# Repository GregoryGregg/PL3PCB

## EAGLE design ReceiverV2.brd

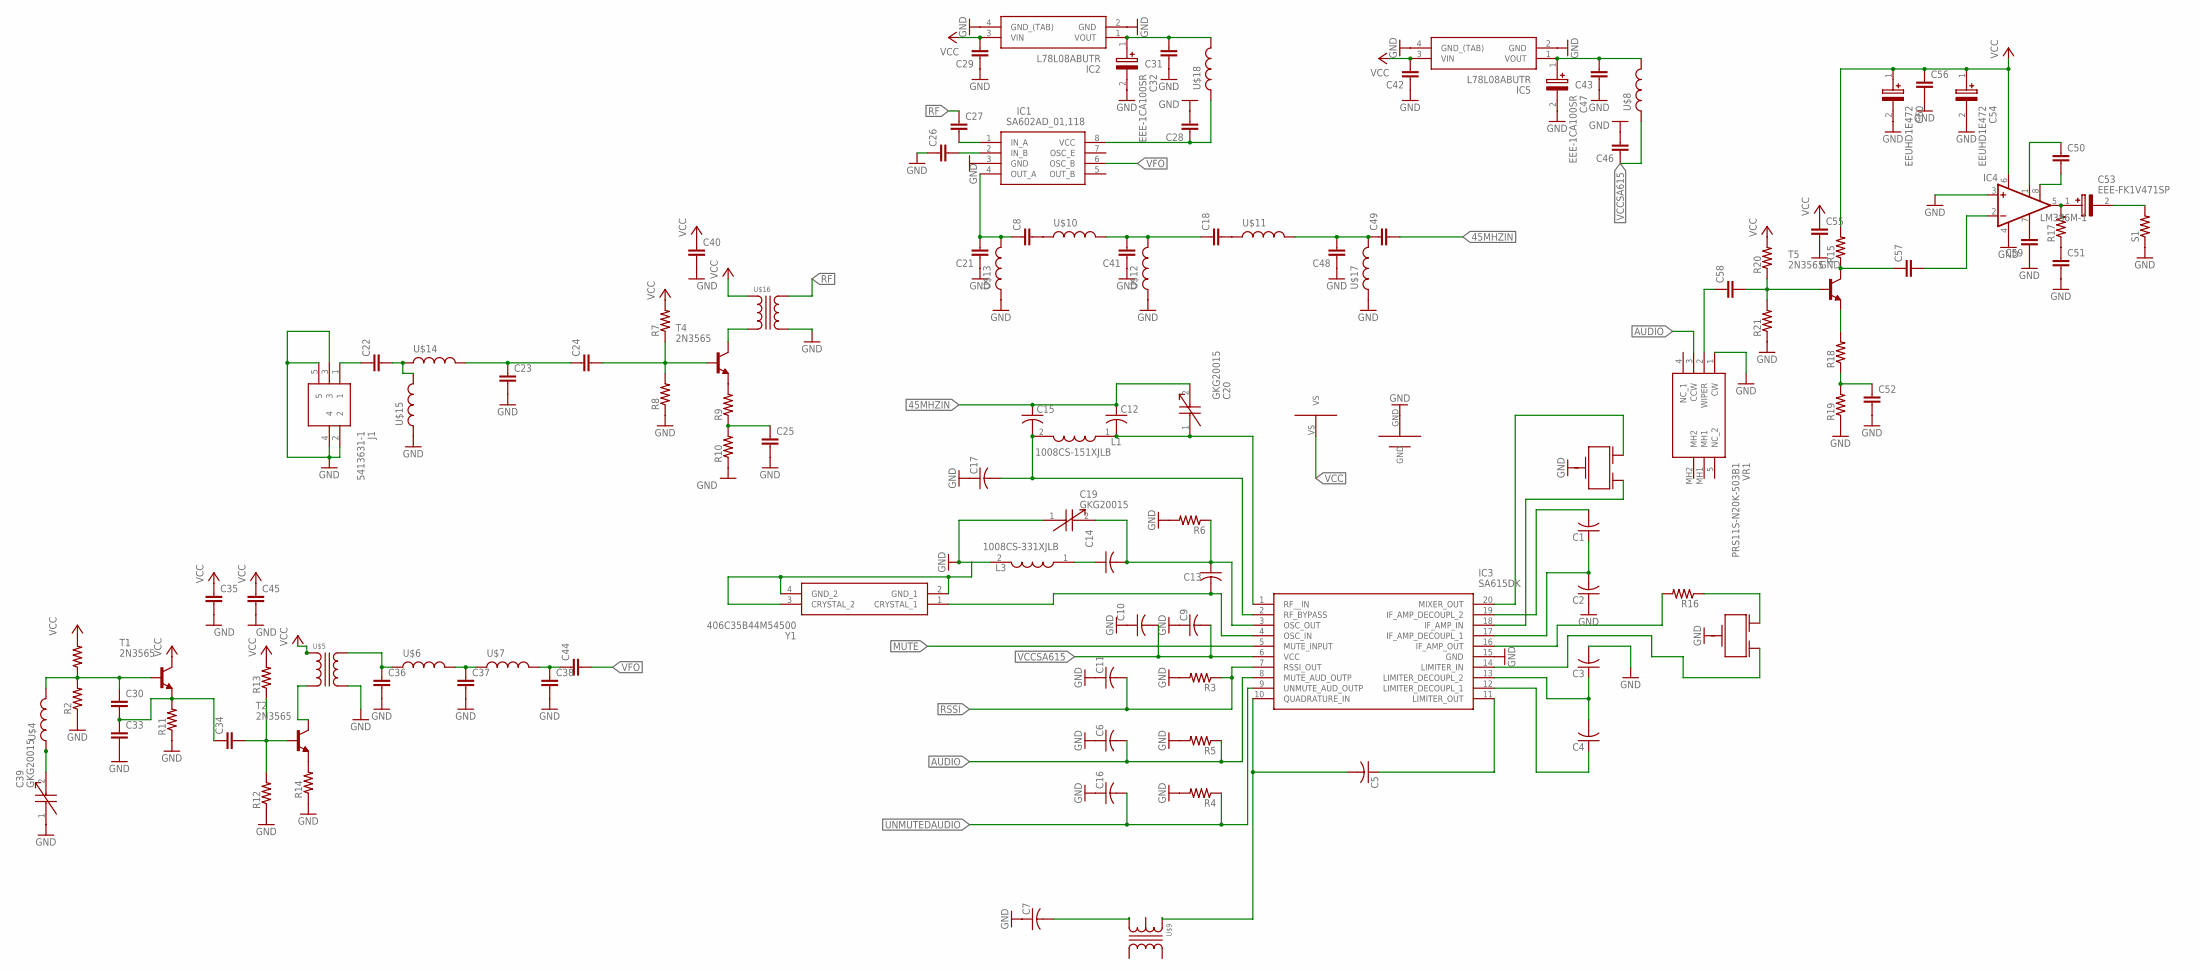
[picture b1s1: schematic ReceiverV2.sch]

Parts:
C1, C2, C3, C4, C5, C6, C7, C9, C10, C11, C12, C13, C14, C15, C16, C17: C-USC0805; C0805
C8, C18, C21, C22, C23, C24, C25, C26, C27, C28, C29, C30, C31, C33, C34, C35, C36, C37, C38, C40, C41, C42, C43, C44, C45, C46, C48, C49, C50, C51, C52, C55, C57, C58, C59: C; C0805
C19, C20, C39: GKG20015
C32, C47: EEE-1CA100SR; SV(B)
C53: EEE-FK1V471SP; CAPAE1030X1050N
C54, C60: EEUHD1E472; CAPPRD750W85D1600H2700
C56: CC1206; C1206
IC1: SA602AD_01,118; SOIC127P600X175-8N
IC2, IC5: L78L08ABUTR; ST-SOT-89
IC3: SA615DK; SOP65P640X150-20N
IC4: LM386M-1; SO08
J1: 5413631-1; 54136311
L1: 1008CS-151XJLB; INDC2928X203N
L3: 1008CS-331XJLB; INDC2928X203N
R1, R2, R3, R4, R5, R6, R7, R8, R9, R10, R11, R12, R13, R14, R15, R16, R17, R18, R19, R20, R21: R-US_R0805; R0805
S1: R-US_0207/5V; 0207/5V
T1, T2, T4, T5: 2N3565; TO92
U$1: ALLIGATORCLIPS; ALLIGATORCONNECTOR
U$2, U$19: CFWLB455KGFA-B0
U$4, U$6, U$7, U$8, U$10, U$11, U$12, U$13, U$14, U$15, U$17, U$18: WOUNDINDUCTOR
U$5, U$16: RFTRANSFORMER; RFTRABSFORMER
U$9: 42IF123
VR1: PRS11S-N20K-503B1; PRS11SN20K503B1
Y1: 406C35B44M54500

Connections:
45MHZIN: C12.1, C15.1, C20.2, C49.2
AUDIO: C6.2, IC3.8 (MUTE_AUD_OUTP), R5.1, VR1.3 (CCW)
GND: C2.1, C3.2, C6.1, C7.1, C9.1, C10.1, C11.1, C16.1, C17.1, C19.1, C21.1, C23.2, C25.2, C26.1, C28.2, C29.1, C31.1, C32.2 (-), C33.2, C35.2, C36.2, C37.2, C38.2, C39.1, C40.2, C41.1, C42.1, C43.1, C45.2, C46.2, C47.2 (-), C48.1, C51.2, C52.2, C54.2 (-), C55.2, C56.2, C59.1, C60.2 (-), IC1.3 (GND), IC2.2 (GND), IC2.4 (GND_(TAB)), IC3.15 (GND), IC4.3 (+IN), IC4.4 (GND), IC5.2 (GND), IC5.4 (GND_(TAB)), J1.2, J1.3, J1.4, J1.5, L3.2, R2.1, R3.2, R4.2, R5.2, R6.2, R8.1, R10.1, R11.1, R12.1, R14.1, R19.1, R21.1, S1.1, U$1.GND, U$5.P$4, U$12.1, U$13.1, U$15.1, U$16.P$4, U$17.1, VR1.1 (CW), Y1.2 (GND_1), Y1.3 (CRYSTAL_2), Y1.4 (GND_2)
MUTE: IC3.5 (MUTE_INPUT)
unnamed: C25.1, R9.1, R10.2
unnamed: C22.1, J1.1
unnamed: C23.1, C24.1, U$14.2
unnamed: C5.2, IC3.10 (QUADRATURE_IN), U$9.P$2
unnamed: C14.1, L3.1
unnamed: C5.1, IC3.11 (LIMITER_OUT)
unnamed: C4.1, IC3.12 (LIMITER_DECOUPL_1)
unnamed: C3.1, C4.2, IC3.13 (LIMITER_DECOUPL_2)
unnamed: C7.2, U$9.P$3
unnamed: IC3.14 (LIMITER_IN), U$2.P$4 (OUT)
unnamed: C15.2, C17.2, IC3.2 (RF_BYPASS), L1.2
unnamed: C13.2, IC3.4 (OSC_IN), Y1.1 (CRYSTAL_1)
unnamed: C13.1, C14.2, C19.2, IC3.3 (OSC_OUT), R6.1
unnamed: IC3.16 (IF_AMP_OUT), R16.2
unnamed: C12.2, C20.1, IC3.1 (RF__IN), L1.1
unnamed: C57.2, IC4.2 (-IN)
unnamed: C1.1, C2.2, IC3.17 (IF_AMP_DECOUPL_1)
unnamed: IC3.18 (IF_AMP_IN), U$19.P$4 (OUT)
unnamed: IC3.20 (MIXER_OUT), U$19.P$1 (IN)
unnamed: C1.2, IC3.19 (IF_AMP_DECOUPL_2)
unnamed: C24.2, R7.1, R8.2, T4.2 (B)
unnamed: R9.2, T4.3 (E)
unnamed: T4.1 (C), U$16.P$1
unnamed: C26.2, IC1.2 (IN_B)
unnamed: C27.2, IC1.1 (IN_A)
unnamed: C8.2, U$10.1
unnamed: C8.1, C21.2, IC1.4 (OUT_A), U$13.2
unnamed: R14.2, T2.3 (E)
unnamed: C30.2, C33.1, C34.1, R11.2, T1.3 (E)
unnamed: C30.1, R1.1, R2.2, T1.2 (B), U$4.2
unnamed: C34.2, R12.2, R13.1, T2.2 (B)
unnamed: C39.2, U$4.1
unnamed: C28.1, IC1.8 (VCC), U$18.1
unnamed: C36.1, U$5.P$3, U$6.1
unnamed: C22.2, U$14.1, U$15.2
unnamed: C37.1, U$6.2, U$7.1
unnamed: C38.1, C44.1, U$7.2
unnamed: T2.1 (C), U$5.P$1
unnamed: C18.2, U$11.1
unnamed: C18.1, C41.2, U$10.2, U$12.2
unnamed: C43.2, C47.1 (+), IC5.1 (VOUT), U$8.2
unnamed: C48.2, C49.1, U$11.2, U$17.2
unnamed: C58.1, VR1.2 (WIPER)
unnamed: C53.1 (+), IC4.5 (OUT), R17.2
unnamed: C51.1, R17.1
unnamed: C31.2, C32.1 (+), IC2.1 (VOUT), U$18.2
unnamed: C50.1, IC4.1 (GAIN)
unnamed: C50.2, IC4.8 (GAIN)
unnamed: C53.2 (-), S1.2
unnamed: C58.2, R20.1, R21.2, T5.2 (B)
unnamed: R18.2, T5.3 (E)
unnamed: C52.1, R18.1, R19.2
unnamed: C57.1, R15.1, T5.1 (C)
unnamed: C59.2, IC4.7 (BYPASS)
unnamed: R16.1, U$2.P$1 (IN)
RF: C27.1, U$16.P$3
RSSI: C11.2, IC3.7 (RSSI_OUT), R3.1
UNMUTEDAUDIO: C16.2, IC3.9 (UNMUTE_AUD_OUTP), R4.1
VCC: C29.2, C35.1, C40.1, C42.2, C45.1, C54.1 (+), C55.1, C56.1, C60.1 (+), IC2.3 (VIN), IC4.6 (VS), IC5.3 (VIN), R1.2, R7.2, R13.2, R15.2, R20.2, T1.1 (C), U$1.VS, U$5.P$2, U$16.P$2
VCCSA615: C9.2, C10.2, C46.1, IC3.6 (VCC), U$8.1
VFO: C44.2, IC1.6 (OSC_B)

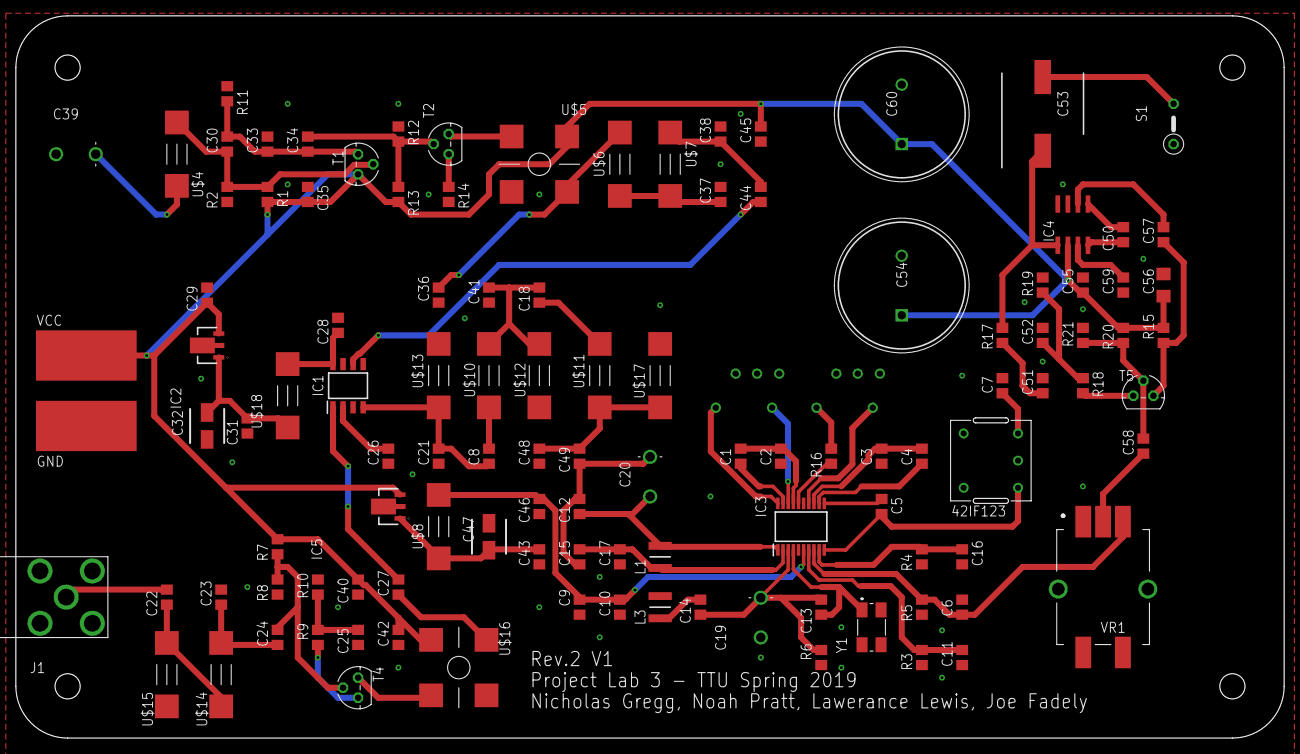
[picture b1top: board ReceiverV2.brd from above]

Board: 2 copper layers, 159.9 x 91.0 mm, 114 parts (0 on the bottom side), 64 nets.

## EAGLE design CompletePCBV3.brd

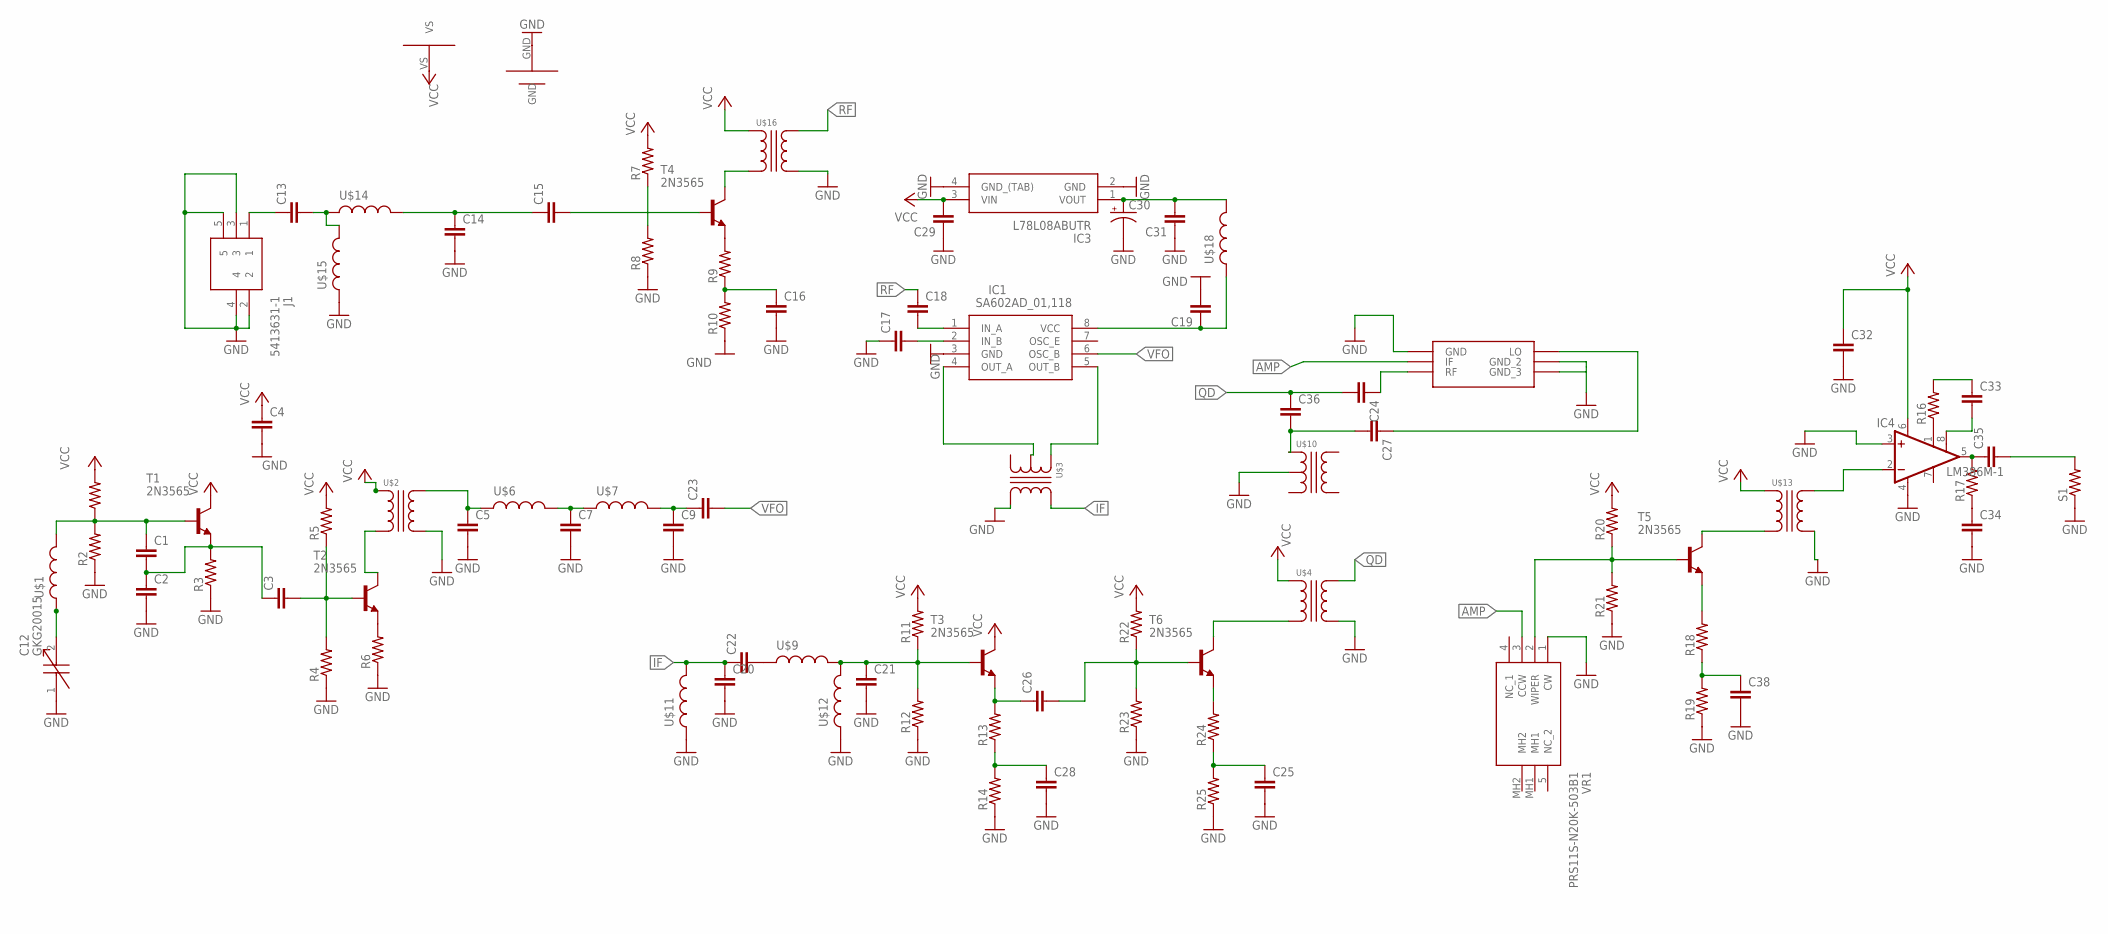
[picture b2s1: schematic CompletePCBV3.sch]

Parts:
C1, C2, C3, C4, C5, C7, C9, C13, C14, C15, C16, C17, C18, C19, C20, C21, C22, C23, C24, C25, C26, C27, C28, C29, C31, C32, C33, C34, C35, C38: C; C0805
C12: GKG20015
C30: CPOL-US175TMP-0808; 175TMP-0808
C36: C-EUC0603; C0603
IC1: SA602AD_01,118; SOIC127P600X175-8N
IC3: L78L08ABUTR; ST-SOT-89
IC4: LM386M-1; SO08
J1: 5413631-1; 54136311
R1, R2, R3, R4, R5, R6, R7, R8, R9, R10, R11, R12, R13, R14, R16, R17, R18, R19, R20, R21, R22, R23, R24, R25: R-US_R0805; R0805
S1: R-US_0207/5V; 0207/5V
T1, T2, T3, T4, T5, T6: 2N3565; TO92
U$1, U$6, U$7, U$9, U$11, U$12, U$14, U$15, U$18: WOUNDINDUCTOR
U$2, U$4, U$13, U$16: RFTRANSFORMER; RFTRABSFORMER
U$3, U$10: 42IF123
U$5: ALLIGATORCLIPS; ALLIGATORCONNECTOR
U$17: ADE-1
VR1: PRS11S-N20K-503B1; PRS11SN20K503B1

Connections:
AMP: U$17.IF, VR1.3 (CCW)
GND: C2.2, C4.2, C5.2, C7.2, C9.2, C12.1, C14.2, C16.2, C17.1, C19.2, C20.2, C21.2, C25.2, C28.2, C29.1, C30.-, C31.1, C32.2, C34.2, C38.2, IC1.3 (GND), IC3.2 (GND), IC3.4 (GND_(TAB)), IC4.3 (+IN), IC4.4 (GND), J1.2, J1.3, J1.4, J1.5, R2.1, R3.1, R4.1, R6.1, R8.1, R10.1, R12.1, R14.1, R19.1, R21.1, R23.1, R25.1, S1.1, U$2.P$4, U$3.P$4, U$4.P$4, U$5.GND, U$10.P$1, U$11.1, U$12.1, U$13.P$4, U$15.1, U$16.P$4, U$17.GND, U$17.GND2 (GND_2), U$17.GND3 (GND_3), VR1.1 (CW)
IF: C20.1, C22.1, U$3.P$5, U$11.2
unnamed: R6.2, T2.3 (E)
unnamed: C30.+, C31.2, IC3.1 (VOUT), U$18.2
unnamed: C1.2, C2.1, C3.1, R3.2, T1.3 (E)
unnamed: C1.1, R1.1, R2.2, T1.2 (B), U$1.2
unnamed: C3.2, R4.2, R5.1, T2.2 (B)
unnamed: C26.2, R22.1, R23.2, T6.2 (B)
unnamed: C22.2, U$9.1
unnamed: C5.1, U$2.P$3, U$6.1
unnamed: R9.2, T4.3 (E)
unnamed: C7.1, U$6.2, U$7.1
unnamed: T2.1 (C), U$2.P$2
unnamed: C12.2, U$1.1
unnamed: C9.1, C23.1, U$7.2
unnamed: C16.1, R9.1, R10.2
unnamed: C13.1, J1.1
unnamed: C14.1, C15.1, U$14.2
unnamed: C15.2, T4.2 (B)
unnamed: R7.1, R8.2
unnamed: T4.1 (C), U$16.P$2
unnamed: IC1.5 (OUT_B), U$3.P$2
unnamed: IC1.4 (OUT_A), U$3.P$1
unnamed: C28.1, R13.1, R14.2
unnamed: C17.2, IC1.2 (IN_B)
unnamed: C18.2, IC1.1 (IN_A)
unnamed: C27.1, U$17.LO
unnamed: T6.1 (C), U$4.P$2
unnamed: C27.2, C36.2, U$10.P$2
unnamed: R20.1, R21.2, T5.2 (B), VR1.2 (WIPER)
unnamed: R18.2, T5.3 (E)
unnamed: C38.1, R18.1, R19.2
unnamed: C21.1, R11.1, R12.2, T3.2 (B), U$9.2, U$12.2
unnamed: T5.1 (C), U$13.P$2
unnamed: C24.1, U$17.RF
unnamed: C19.1, IC1.8 (VCC), U$18.1
unnamed: IC4.2 (-IN), U$13.P$3
unnamed: C13.2, U$14.1, U$15.2
unnamed: R24.2, T6.3 (E)
unnamed: C25.1, R24.1, R25.2
unnamed: C26.1, R13.2, T3.3 (E)
unnamed: IC4.1 (GAIN), R16.1
unnamed: C35.1, IC4.5 (OUT), R17.2
unnamed: C34.1, R17.1
unnamed: C33.1, R16.2
unnamed: C33.2, IC4.8 (GAIN)
unnamed: C35.2, S1.2
QD: C24.2, C36.1, U$4.P$3
RF: C18.1, U$16.P$3
VCC: C4.1, C29.2, C32.1, IC3.3 (VIN), IC4.6 (VS), R1.2, R5.2, R7.2, R11.2, R20.2, R22.2, T1.1 (C), T3.1 (C), U$2.P$1, U$4.P$1, U$5.VS, U$13.P$1, U$16.P$1
VFO: C23.2, IC1.6 (OSC_B)

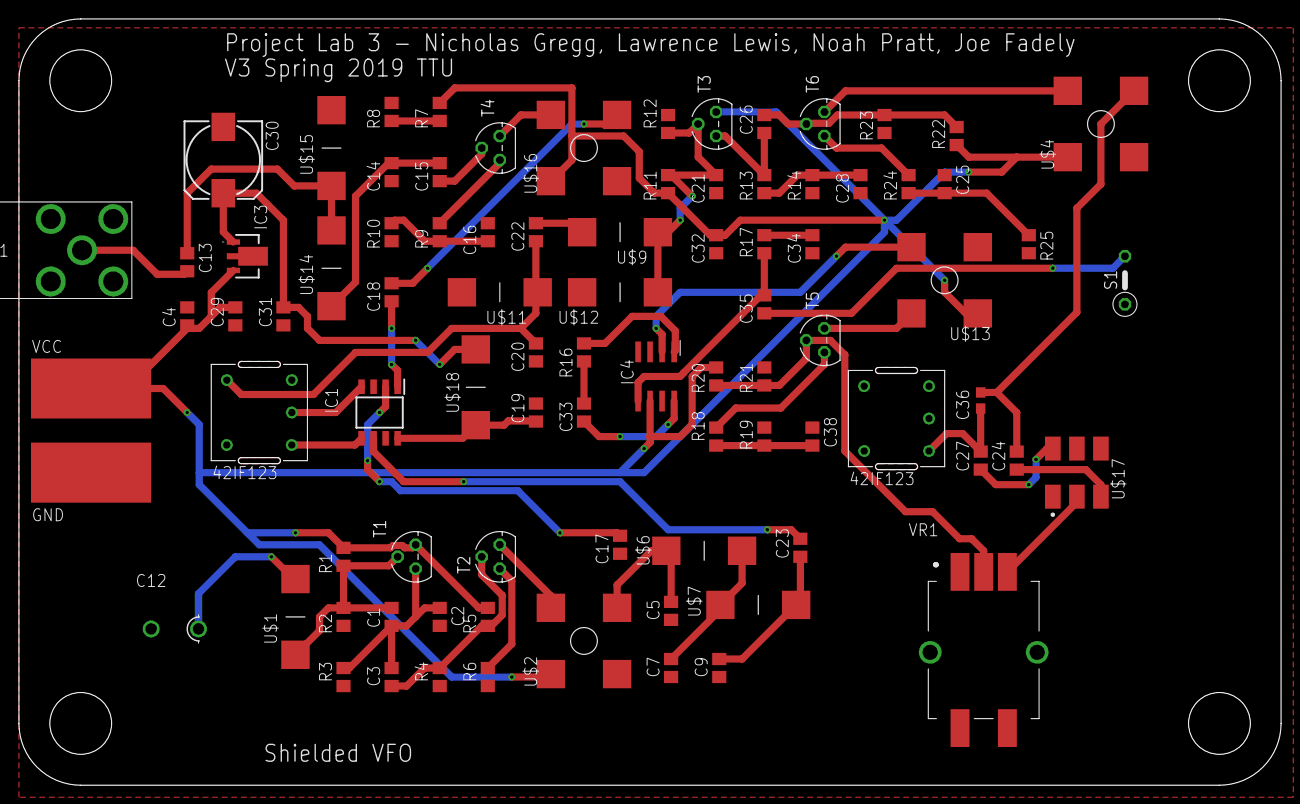
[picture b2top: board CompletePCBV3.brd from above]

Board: 2 copper layers, 133.2 x 80.8 mm, 86 parts (0 on the bottom side), 52 nets.

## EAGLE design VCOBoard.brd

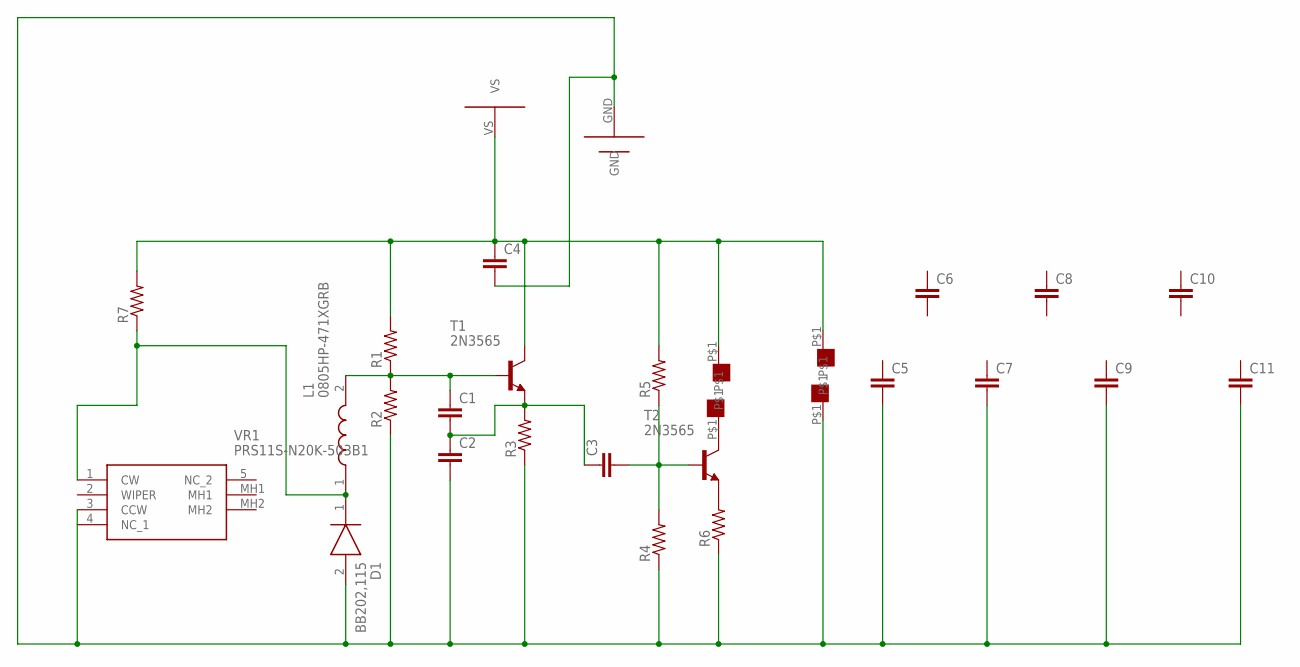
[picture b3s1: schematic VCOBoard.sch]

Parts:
C1, C2, C3, C4, C5, C6, C7, C8, C9, C10, C11: C; C0805
D1: BB202,115; SODFL1608X65N
L1: 0805HP-471XGRB; INDPM2217X155N
R1, R2, R3, R4, R5, R6, R7: R-US_R0805; R0805
T1, T2: 2N3565; TO92
U$1, U$2, U$3, U$4: PAD
U$5: ALLIGATORCLIPS; ALLIGATORCONNECTOR
VR1: PRS11S-N20K-503B1; PRS11SN20K503B1

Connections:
unnamed: R6.2, T2.3 (E)
unnamed: C4.1, R1.2, R5.2, R7.2, T1.1 (C), U$2.P$1, U$3.P$1, U$5.VS
unnamed: C1.2, C2.1, C3.1, R3.2, T1.3 (E)
unnamed: C1.1, L1.2, R1.1, R2.2, T1.2 (B)
unnamed: C3.2, R4.2, R5.1, T2.2 (B)
unnamed: C2.2, C4.2, C5.2, C7.2, C9.2, C11.2, D1.2 (A), R2.1, R3.1, R4.1, R6.1, U$4.P$1, U$5.GND, VR1.3 (CCW)
unnamed: T2.1 (C), U$1.P$1
unnamed: D1.1 (K), L1.1, R7.1, VR1.1 (CW)

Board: 2 copper layers, 28 parts (0 on the bottom side), 8 nets, no tracks yet.

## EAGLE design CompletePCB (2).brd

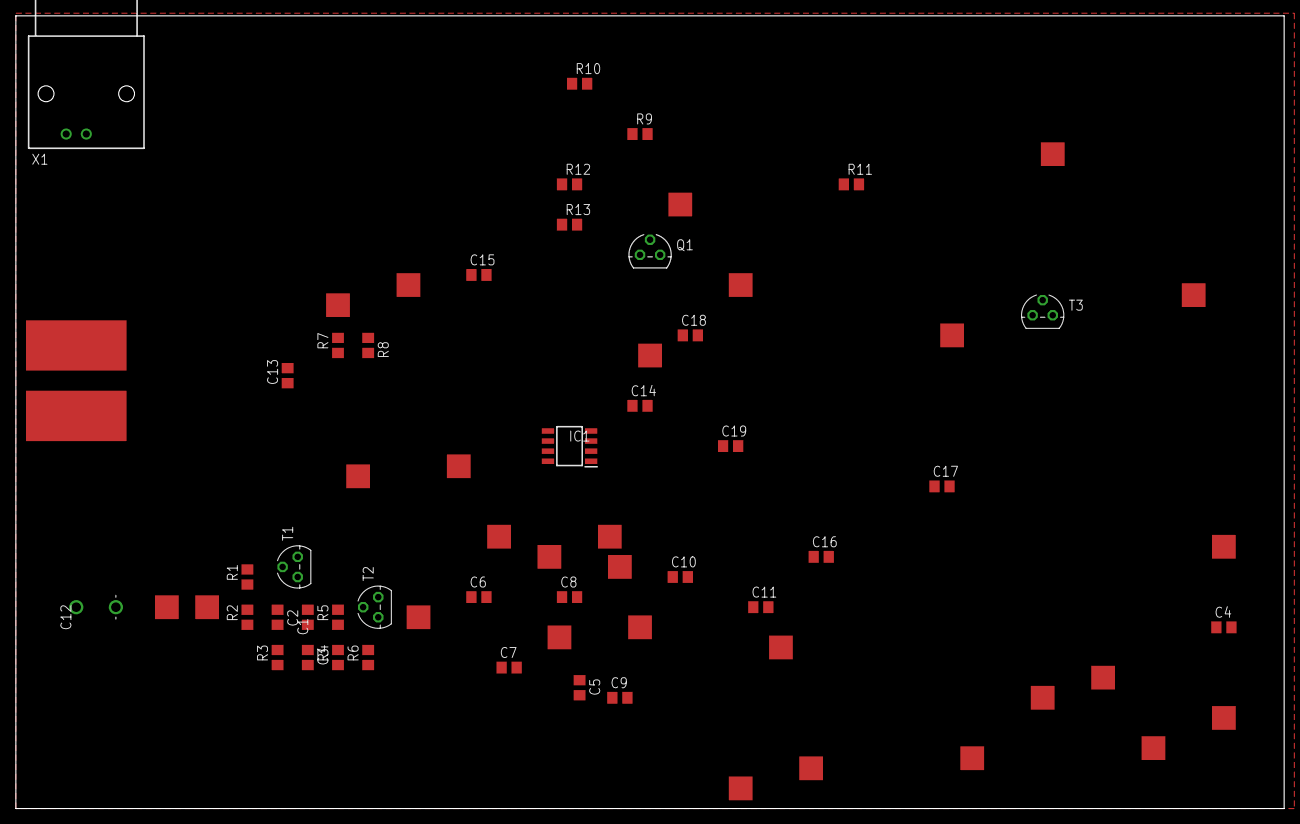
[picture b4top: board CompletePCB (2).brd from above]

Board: 2 copper layers, 160.0 x 100.0 mm, 67 parts (0 on the bottom side), 27 nets, no tracks yet.

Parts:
C1, C2, C3, C4, C5, C6, C7, C8, C9, C10, C11, C13, C14, C15, C16, C17, C18, C19: C0805
C12: GKG20015
IC1: SA602AD_01,118; SOIC127P600X175-8N
Q1: 2N3704; TO92C
R1, R2, R3, R4, R5, R6, R7, R8, R9, R10, R11, R12, R13: R0805
T1, T2, T3: 2N3565; TO92
U$1, U$2, U$3, U$4, U$6, U$7, U$8, U$9, U$10, U$11, U$12, U$13, U$14, U$15, U$16, U$17, U$18, U$19, U$20, U$21, U$22, U$23, U$24, U$25, U$26, U$27, U$28, U$29: PAD
U$5: ALLIGATORCLIPS; ALLIGATORCONNECTOR
X1: 1-227161-0; AMP_227161

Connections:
GND: C2.2, C4.2, C5.2, C7.2, C9.2, C11.2, C12.1, C13.2, C14.2, C16.2, C17.1, IC1.3, R2.1, R3.1, R4.1, R6.1, R8.1, R10.1, R12.1, R13.1, U$4.P$1, U$5.GND, U$15.P$1, U$21.P$1, U$24.P$1, U$28.P$1, X1.2
unnamed: R6.2, T2.3
unnamed: C4.1, IC1.8, R1.2, R5.2, R7.2, R11.2, T1.1, U$2.P$1, U$5.VS, U$18.P$1, U$26.P$1
unnamed: C1.2, C2.1, C3.1, R3.2, T1.3
unnamed: C1.1, R1.1, R2.2, T1.2, U$7.P$1
unnamed: C3.2, R4.2, R5.1, T2.2
unnamed: R13.2, T3.3
unnamed: T2.1, U$1.P$1
unnamed: C5.1, C6.2, U$3.P$1, U$8.P$1
unnamed: Q1.E, R9.2
unnamed: C8.2, C9.1, C10.1, U$11.P$1, U$12.P$1
unnamed: C10.2, C11.1, IC1.6, U$13.P$1
unnamed: C12.2, U$6.P$1
unnamed: C6.1, C7.1, C8.1, U$9.P$1, U$10.P$1
unnamed: C16.1, R9.1, R10.2
unnamed: C13.1, U$14.P$1, U$16.P$1, X1.1
unnamed: C14.1, C15.1, U$17.P$1
unnamed: C15.2, Q1.B
unnamed: R7.1, R8.2
unnamed: Q1.C, U$19.P$1
unnamed: C19.2, IC1.5, U$23.P$1
unnamed: C19.1, IC1.4, U$22.P$1
unnamed: C18.1, U$20.P$1
unnamed: C17.2, IC1.2
unnamed: C18.2, IC1.1
unnamed: T3.1, U$27.P$1
unnamed: R11.1, R12.2, T3.2

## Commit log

2019-06-10 Changes Made over time
